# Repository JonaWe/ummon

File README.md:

# ummon

ummon (from German *Umgebungsmonitor*, "environment monitor") is an ESP32-C6 based environmental sensor board with USB-C power. It reads several environmental sensors over I²C and drives an e-paper display (a 7.5" Waveshare panel in this build). The board is a custom 4-layer PCB designed in KiCad, powered from USB-C with on-board 3.3 V regulation.

## Features

- MCU: ESP32-C6-WROOM-1 (Wi-Fi 6, Bluetooth LE, Zigbee/Thread)
- Sensors over I²C:
  - SHT41 for temperature and humidity
  - SCD41 for CO₂
  - SGP41 for VOC / air quality
- Display: e-paper via an on-board boost converter for the panel supply rails (7.5" Waveshare V2 used here)
- Power: USB-C input, AMS1117 3.3 V LDO, TVS/ESD protection on VBUS and the USB data lines

## Repository structure

```
├── hardware/      KiCad project (schematic, PCB, footprints, datasheets)
├── firmware/      ESP32-C6 firmware (planned)
└── mechanical/    3D-printed enclosure (planned)
```

## Hardware

The PCB uses a 4-layer stackup:

| Layer   | Purpose              |
|---------|----------------------|
| Top     | Signals + components |
| Inner 1 | Continuous GND plane |
| Inner 2 | 3.3 V plane          |
| Bottom  | Signals              |

## Status

- [x] Schematic
- [x] PCB layout
- [ ] Firmware
- [ ] Enclosure

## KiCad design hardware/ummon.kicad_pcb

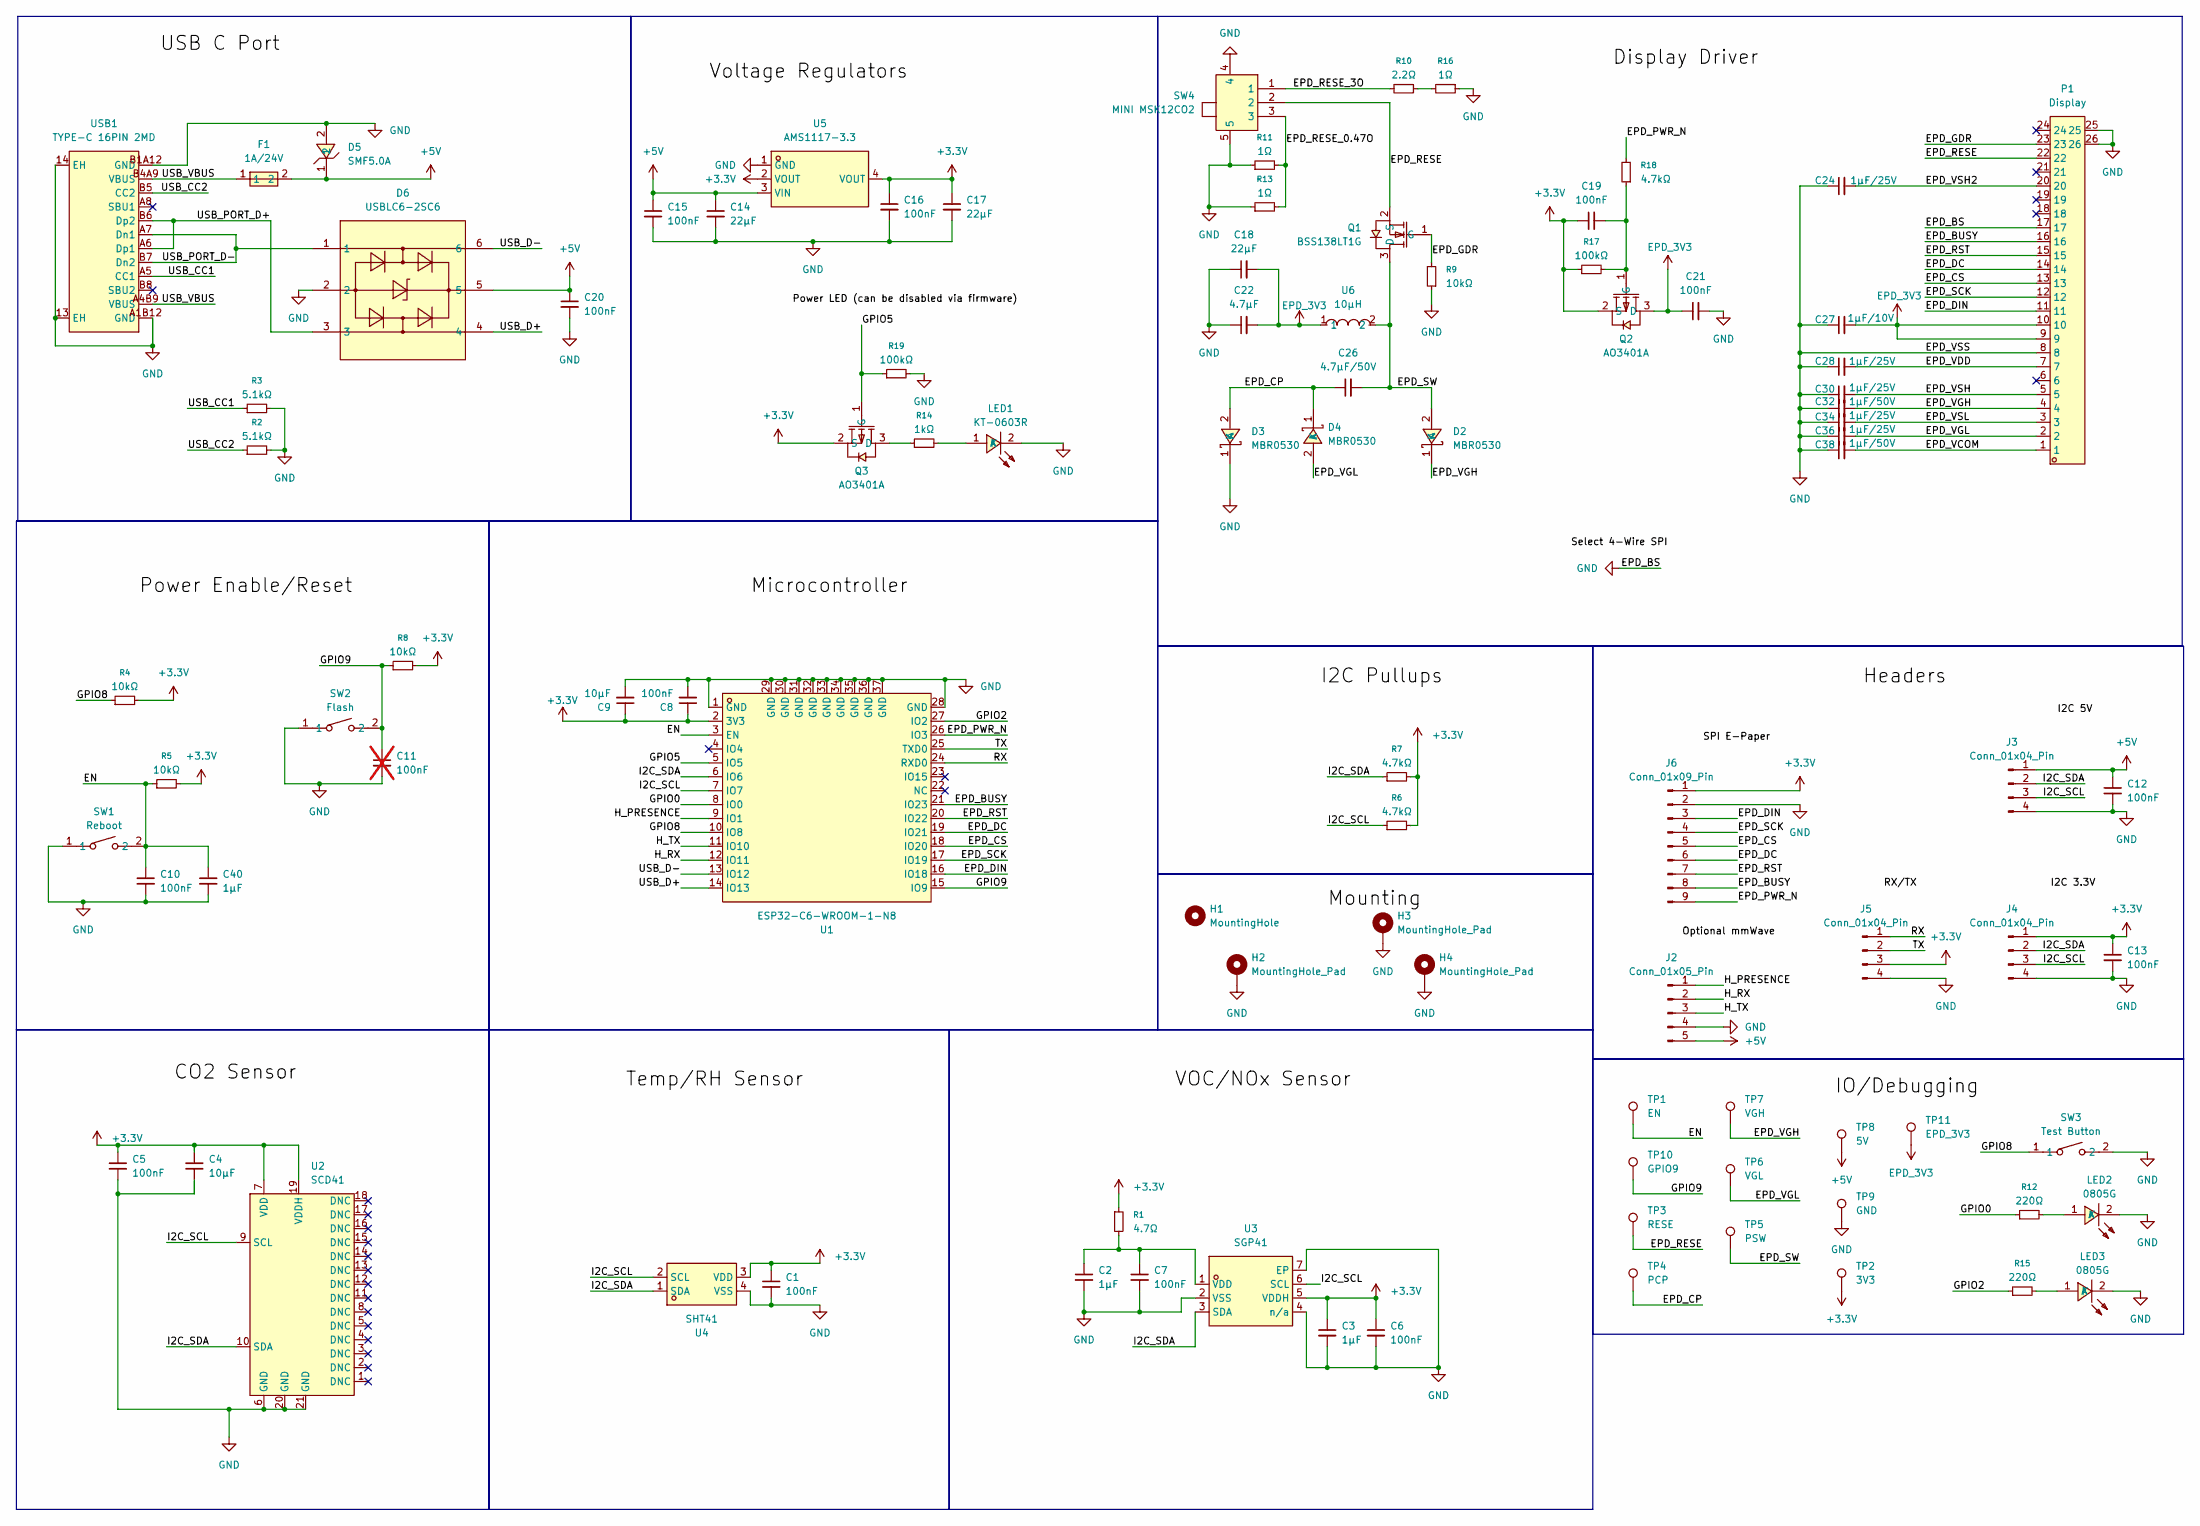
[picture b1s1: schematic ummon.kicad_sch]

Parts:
C1, C5, C6, C7, C8, C10, C12, C13, C15, C16, C19, C20, C21: 100nF; C_0805_2012Metric; LCSC Part C49678
C2, C3, C40: 1µF; C_0805_2012Metric; LCSC Part C28323
C4, C9: 10µF; C_0805_2012Metric; LCSC Part C440198
C11: 100nF; C_0805_2012Metric; LCSC Part C49678; not fitted
C14, C17, C18: 22µF; C_1206_3216Metric; LCSC Part C12891
C22: 4.7μF; C_1206_3216Metric; LCSC Part C29823
C24, C28, C30, C34, C36: 1μF/25V; C_0805_2012Metric; LCSC Part C28323
C26: 4.7μF/50V; C_1206_3216Metric; LCSC Part C29823
C27: 1μF/10V; C_0805_2012Metric; LCSC Part C28323
C32, C38: 1μF/50V; C_0805_2012Metric; LCSC Part C28323
D2, D3, D4: MBR0530; SOD-123_L2.8-W1.8-LS3.7-RD; MPN LMBR0530T1G; LCSC Part C18863
D5: SMF5.0A; SOD-123F_L2.8-W1.8-LS3.7-RD; MPN SMF5.0A; LCSC Part C169426
D6: USBLC6-2SC6; SOT-23-6_L2.9-W1.6-P0.95-LS2.8-BL; MPN USBLC6-2SC6; LCSC Part C7519
F1: 1A/24V; F1206; MPN 1206L100/24NR; LCSC Part C7542957
H1: MountingHole; MountingHole_3.2mm_M3
H2, H3, H4: MountingHole_Pad; MountingHole_3.2mm_M3_Pad
J2: Conn_01x05_Pin; PinHeader_1x05_P2.54mm_Vertical; LCSC Part C492404
J3, J4, J5: Conn_01x04_Pin; PinHeader_1x04_P2.54mm_Vertical; LCSC Part C2691448
J6: Conn_01x09_Pin; PinHeader_1x09_P2.54mm_Vertical
LED1: KT-0603R; LED-SMD_L1.6-W0.8-R-RD; MPN KT-0603R; LCSC Part C2286
LED2, LED3: 0805G; LED0805-R-RD; MPN KT-0805G; LCSC Part C2297
P1: Display; FPC-SMD_AFC11-S24ICC-00; MPN AFC11-S24ICC-00; LCSC Part C11075
Q1: BSS138LT1G; SOT-23-3_L2.9-W1.6-P1.90-LS2.8-BR; MPN BSS138LT1G; LCSC Part C82045
Q2, Q3: AO3401A; SOT-23_L2.9-W1.3-P1.90-LS2.4-BR; MPN AO3401A; LCSC Part C15127
R1: 4.7Ω; R_0805_2012Metric; LCSC Part C17675
R2, R3: 5.1kΩ; R_0805_2012Metric; LCSC Part C27834
R4, R5, R8, R9: 10kΩ; R_0805_2012Metric; LCSC Part C17414
R6, R7, R18: 4.7kΩ; R_0805_2012Metric; LCSC Part C17673
R10: 2.2Ω; R_0805_2012Metric; LCSC Part C17521
R11, R13, R16: 1Ω; R_0805_2012Metric; LCSC Part C25271
R12, R15: 220Ω; R_0805_2012Metric; LCSC Part C17557
R14: 1kΩ; R_0805_2012Metric; LCSC Part C17513
R17, R19: 100kΩ; R_0805_2012Metric; LCSC Part C149504
SW1: Reboot; SW-SMD_L3.9-W3.0-P4.45; MPN TS-1088-AR02016; LCSC Part C720477
SW2: Flash; SW-SMD_L3.9-W3.0-P4.45; MPN TS-1088-AR02016; LCSC Part C720477
SW3: Test Button; SW-SMD_L3.9-W3.0-P4.45; MPN TS-1088-AR02016; LCSC Part C720477
SW4: MINI MSK12CO2; SW-SMD_MSK12CO2; MPN MINI MSK12CO2; LCSC Part C2681570
TP1: EN; TestPoint_Pad_D1.0mm
TP2: 3V3; TestPoint_Pad_D1.0mm
TP3: RESE; TestPoint_Pad_D1.0mm
TP4: PCP; TestPoint_Pad_D1.0mm
TP5: PSW; TestPoint_Pad_D1.0mm
TP6: VGL; TestPoint_Pad_D1.0mm
TP7: VGH; TestPoint_Pad_D1.0mm
TP8: 5V; TestPoint_Pad_D1.0mm
TP9: GND; TestPoint_Pad_D1.0mm
TP10: GPIO9; TestPoint_Pad_D1.0mm
TP11: EPD_3V3; TestPoint_Pad_D1.0mm
U1: ESP32-C6-WROOM-1-N8; ESP32-C6-WROOM-1; MPN ESP32-C6-WROOM-1-N8; LCSC Part C5366877
U2: SCD41; LGA-20_L10.1-W10.1-P1.25-TL; MPN SCD41-D-R2; LCSC Part C3659294
U3: SGP41; DFN-6_L2.4-W2.4-P0.80-TL-EP; MPN SGP41-D-R4; LCSC Part C3659325
U4: SHT41; DFN-4_L1.5-W1.5-SHT41-AD1B-R2; MPN SHT41-AD1B-R2; LCSC Part C7461861
U5: AMS1117-3.3; SOT-223-3_L6.5-W3.4-P2.30-LS7.0-BR; MPN AMS1117-3.3; LCSC Part C6186
U6: 10μH; IND-SMD_L4.5-W4.0; MPN CY43-10UH; LCSC Part C2929419
USB1: TYPE-C 16PIN 2MD; USB-C-SMD_TYPE-C-16PIN-2MD-073; MPN TYPE-C 16PIN 2MD(073); LCSC Part C2765186

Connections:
+3.3V: C1.1, C3.1, C4.1, C5.1, C6.1, C8.1, C9.1, C13.1, C16.1, C17.1, C19.1, J4.1, J5.3, J6.1, Q2.2 (S), Q3.2 (S), R1.1, R4.2, R5.2, R6.2, R7.2, R8.2, R17.1, TP2.1 (1_1), U1.2 (3V3), U2.7 (VDD), U2.19 (VDDH), U3.5 (VDDH), U4.3 (VDD), U5.2 (VOUT), U5.4 (VOUT)
+5V: C12.1, C14.1, C15.1, C20.1, D5.1, D6.5, F1.2, J2.5, J3.1, TP8.1 (1_1), U5.3 (VIN)
/EN: C10.1, C40.1, R5.1, SW1.2, TP1.1 (1_1), U1.3 (EN)
/EPD_BUSY: J6.8, P1.16, U1.21 (IO23)
/EPD_CP: C26.1, D3.2 (A), D4.1 (K), TP4.1 (1_1)
/EPD_CS: J6.5, P1.13, U1.18 (IO20)
/EPD_DC: J6.6, P1.14, U1.19 (IO21)
/EPD_DIN: J6.3, P1.11, U1.16 (IO18)
/EPD_GDR: P1.23, Q1.1 (G), R9.2
/EPD_PWR_N: J6.9, R18.2, U1.26 (IO3)
/EPD_RESE: P1.22, Q1.2 (S), SW4.2, TP3.1 (1_1)
/EPD_RESE_0.47O: R11.2, R13.2, SW4.3
/EPD_RESE_3O: R10.2, SW4.1
/EPD_RST: J6.7, P1.15, U1.20 (IO22)
/EPD_SCK: J6.4, P1.12, U1.17 (IO19)
/EPD_SW: C26.2, D2.2 (A), Q1.3 (D), TP5.1 (1_1), U6.2
/EPD_VCOM: C38.2, P1.1
/EPD_VDD: C28.2, P1.7
/EPD_VGH: C32.2, D2.1 (K), P1.4, TP7.1 (1_1)
/EPD_VGL: C36.2, D4.2 (A), P1.2, TP6.1 (1_1)
/EPD_VSH: C30.2, P1.5
/EPD_VSH2: C24.2, P1.20
/EPD_VSL: C34.2, P1.3
/GPIO0: R12.1, U1.8 (IO0)
/GPIO2: R15.1, U1.27 (IO2)
/GPIO5: Q3.1 (G), R19.1, U1.5 (IO5)
/GPIO8: R4.1, SW3.1, U1.10 (IO8)
/GPIO9: C11.1, R8.1, SW2.2, TP10.1 (1_1), U1.15 (IO9)
/H_PRESENCE: J2.1, U1.9 (IO1)
/H_RX: J2.2, U1.12 (IO11)
/H_TX: J2.3, U1.11 (IO10)
/I2C_SCL: J3.3, J4.3, R6.1, U1.7 (IO7), U2.9 (SCL), U3.6 (SCL), U4.2 (SCL)
/I2C_SDA: J3.2, J4.2, R7.1, U1.6 (IO6), U2.10 (SDA), U3.3 (SDA), U4.1 (SDA)
/RX: J5.1, U1.24 (RXD0)
/TX: J5.2, U1.25 (TXD0)
/USB_CC1: R3.1, USB1.A5 (CC1)
/USB_CC2: R2.1, USB1.B5 (CC2)
/USB_D+: D6.4, U1.14 (IO13)
/USB_D-: D6.6, U1.13 (IO12)
/USB_PORT_D+: D6.3, USB1.A6 (Dp1), USB1.B6 (Dp2)
/USB_PORT_D-: D6.1, USB1.A7 (Dn1), USB1.B7 (Dn2)
/USB_VBUS: F1.1, USB1.A4B9 (VBUS), USB1.B4A9 (VBUS)
EPD_3V3: C18.2, C21.1, C22.2, C27.2, P1.9, P1.10, Q2.3 (D), TP11.1 (1_1), U6.1
GND: C1.2, C2.2, C3.2, C4.2, C5.2, C6.2, C7.2, C8.2, C9.2, C10.2, C11.2, C12.2, C13.2, C14.2, C15.2, C16.2, C17.2, C18.1, C20.2, C21.2, C22.1, C24.1, C27.1, C28.1, C30.1, C32.1, C34.1, C36.1, C38.1, C40.2, D3.1 (K), D5.2, D6.2, H2.1 (1_1), H3.1 (1_1), H4.1 (1_1), J2.4, J3.4, J4.4, J5.4, J6.2, LED1.2 (K), LED2.2 (K), LED3.2 (K), P1.8, P1.17, P1.25, P1.26, R2.2, R3.2, R9.1, R11.1, R13.1, R16.1, R19.2, SW1.1, SW2.1, SW3.2, SW4.4, SW4.5, TP9.1 (1_1), U1.1 (GND), U1.28 (GND), U1.29 (GND), U1.30 (GND), U1.31 (GND), U1.32 (GND), U1.33 (GND), U1.34 (GND), U1.35 (GND), U1.36 (GND), U1.37 (GND), U2.6 (GND), U2.20 (GND), U2.21 (GND), U3.2 (VSS), U3.4 (n/a), U3.7 (EP), U4.4 (VSS), U5.1 (GND), USB1.13 (EH), USB1.14 (EH), USB1.A1B12 (GND), USB1.B1A12 (GND)
unnamed: LED1.1 (A), R14.2
unnamed: LED2.1 (A), R12.2
unnamed: LED3.1 (A), R15.2
unnamed: C19.2, Q2.1 (G), R17.2, R18.1
unnamed: Q3.3 (D), R14.1
unnamed: R10.1, R16.2
unnamed: C2.1, C7.1, R1.2, U3.1 (VDD)

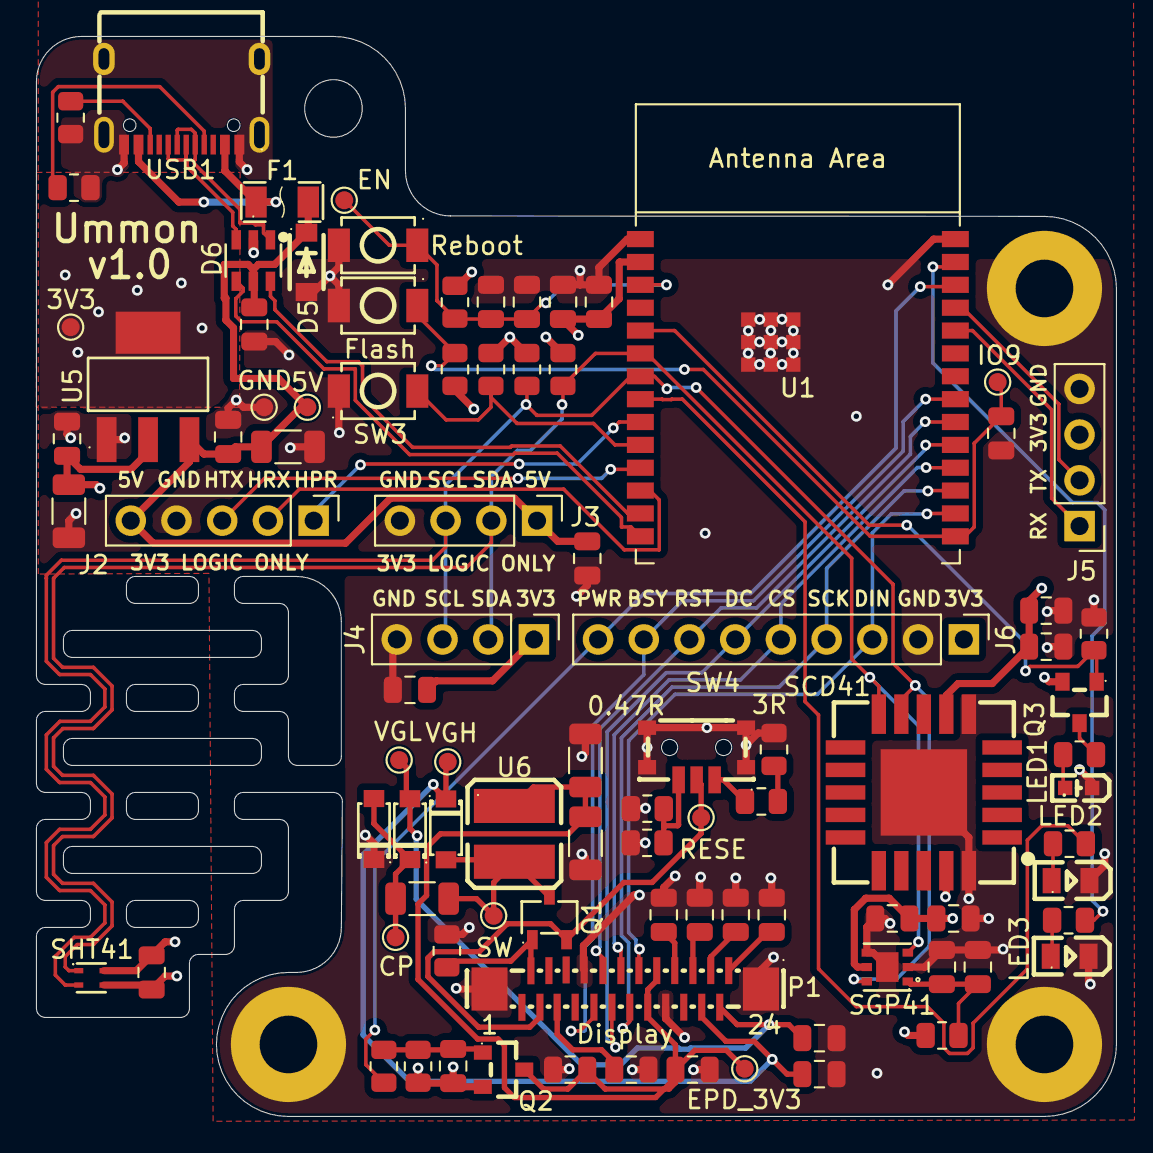
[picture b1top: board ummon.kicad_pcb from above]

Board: 4 copper layers, 60.0 x 60.0 mm, 95 parts (0 on the bottom side), 51 nets.

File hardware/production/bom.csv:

Designator,Footprint,Quantity,Value,LCSC Part #
"C1, C10, C12, C13, C15, C16, C19, C20, C21, C5, C6, C7, C8",0805,13,100nF,C49678
"C14, C17, C18",1206,3,22µF,C12891
"C2, C3, C40",0805,3,1µF,C28323
C22,1206,1,4.7μF,C29823
"C24, C28, C30, C34, C36",0805,5,1μF/25V,C28323
C26,1206,1,4.7μF/50V,C29823
C27,0805,1,1μF/10V,C28323
"C32, C38",0805,2,1μF/50V,C28323
"C4, C9",0805,2,10µF,C440198
"D2, D3, D4",SOD-123_L2.8-W1.8-LS3.7-RD,3,MBR0530,C18863
D5,SOD-123F_L2.8-W1.8-LS3.7-RD,1,SMF5.0A,C169426
D6,SOT-23-6_L2.9-W1.6-P0.95-LS2.8-BL,1,USBLC6-2SC6,C7519
F1,F1206,1,1A/24V,C7542957
LED1,LED-SMD_L1.6-W0.8-R-RD,1,KT-0603R,C2286
"LED2, LED3",LED0805-R-RD,2,0805G,C2297
P1,FPC-SMD_AFC11-S24ICC-00,1,Display,C11075
Q1,SOT-23-3_L2.9-W1.6-P1.90-LS2.8-BR,1,BSS138LT1G,C82045
"Q2, Q3",SOT-23_L2.9-W1.3-P1.90-LS2.4-BR,2,AO3401A,C15127
R1,0805,1,4.7Ω,C17675
R10,0805,1,2.2Ω,C17521
"R11, R13, R16",0805,3,1Ω,C25271
"R12, R15",0805,2,220Ω,C17557
R14,0805,1,1kΩ,C17513
"R17, R19",0805,2,100kΩ,C149504
"R18, R6, R7",0805,3,4.7kΩ,C17673
"R2, R3",0805,2,5.1kΩ,C27834
"R4, R5, R8, R9",0805,4,10kΩ,C17414
SW1,SW-SMD_L3.9-W3.0-P4.45,1,Reboot,C720477
SW2,SW-SMD_L3.9-W3.0-P4.45,1,Flash,C720477
SW3,SW-SMD_L3.9-W3.0-P4.45,1,Test Button,C720477
SW4,SW-SMD_MSK12CO2,1,MINI MSK12CO2,C2681570
U1,ESP32-C6-WROOM-1,1,ESP32-C6-WROOM-1-N8,C5366877
U2,LGA-20_L10.1-W10.1-P1.25-TL,1,SCD41,C3659294
U3,DFN-6_L2.4-W2.4-P0.80-TL-EP,1,SGP41,C3659325
U4,DFN-4_L1.5-W1.5-SHT41-AD1B-R2,1,SHT41,C7461861
U5,SOT-223-3_L6.5-W3.4-P2.30-LS7.0-BR,1,AMS1117-3.3,C6186
U6,IND-SMD_L4.5-W4.0,1,10μH,C2929419
USB1,USB-C-SMD_TYPE-C-16PIN-2MD-073,1,TYPE-C 16PIN 2MD,C2765186

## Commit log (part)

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2026-06-22 :tada: Initialize kicad project
2026-06-27 :sparkles: Add nix flake to obtain kicad library from jlc
2026-06-27 :sparkles: Initialize kicad project
2026-06-27 :sparkles: Add gitignore
2026-06-27 :sparkles: Add kicad library for sensors and esp32-c6-wroom
2026-06-27 :sparkles: Add datasheets
2026-06-28 :sparkles: Add reccomended sensor setups
2026-06-28 :sparkles: Add microcontroller with boot/reset pins
